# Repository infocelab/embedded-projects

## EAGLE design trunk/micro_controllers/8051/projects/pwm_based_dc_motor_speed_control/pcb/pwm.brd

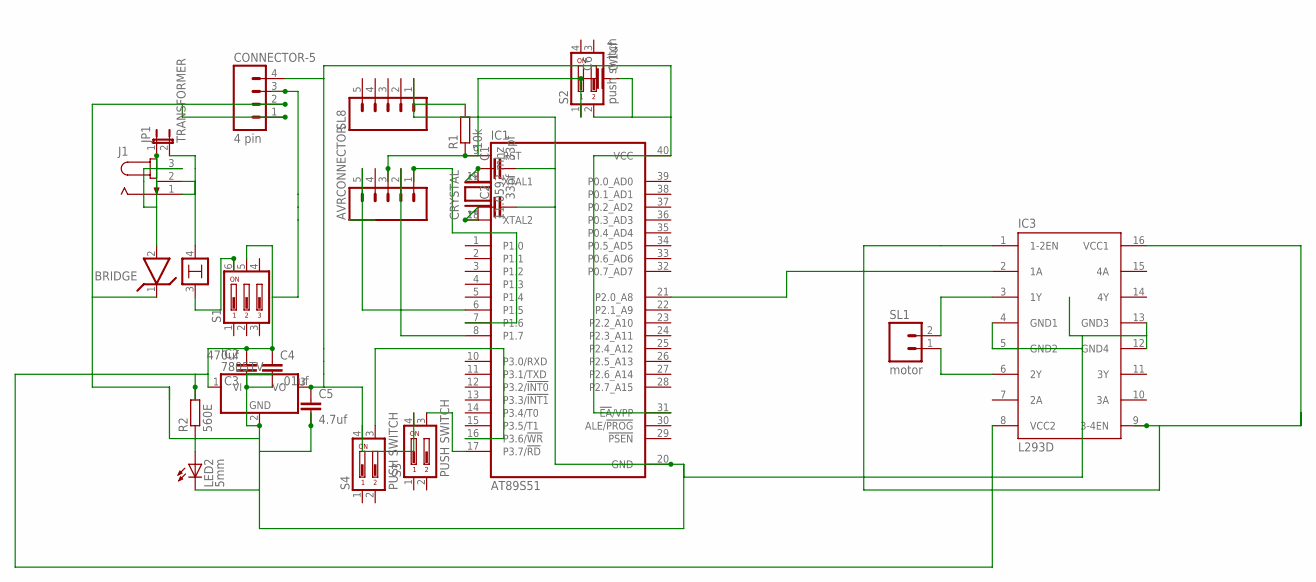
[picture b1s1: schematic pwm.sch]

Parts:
AVRCONNECTOR: M05; 05P
BRIDGE: LM399H; TO39/4
C1, C2: 33pf; C025-024X044
C3: 470uf; C5B7.2
C4: .01uf; C2.5-3
C5: 4.7uf; C2.5-3
C6: 0.1uf; C2.5-3
CONNECTOR-5: 4 pin; 04P
CRYSTAL: 11.0592 mhz; QS
IC1: AT89S51; DIL40
IC2: 7805TV; TO220V
IC3: L293D; DIL16
J1: JACK-PLUG0; SPC4077
JP1: TRANSFORMER; JP1
LED2: 5mm; LED5MM
R1: 10k; 0204/7
R2: 560E; 0204/7
S1: DA03; DA-03
S2: push switch; DP-02
S3, S4: PUSH SWITCH; DS-02
SL1: motor; 02P
SL8: M05; 05P

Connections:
unnamed: C2.1, CRYSTAL.1, IC1.18 (XTAL2)
unnamed: C1.1, CRYSTAL.2, IC1.19 (XTAL1)
unnamed: IC1.17 (P3.7/!RD), S3.3
unnamed: C3.2, C4.1, CONNECTOR-5.3, IC2.1 (VI), IC3.8 (VCC2), R2.2, S1.5
unnamed: BRIDGE.2, J1.3, JP1.1
unnamed: IC3.6 (2Y), SL1.1
unnamed: IC3.3 (1Y), SL1.2
unnamed: BRIDGE.1, CONNECTOR-5.1, CONNECTOR-5.2
unnamed: IC1.16 (P3.6/!WR), S4.3
unnamed: AVRCONNECTOR.3, C6.1, IC1.9 (RST), R1.1, S2.1
unnamed: AVRCONNECTOR.1, IC1.7 (P1.6)
unnamed: BRIDGE.4, J1.1, J1.2, JP1.2
unnamed: C1.2, C2.2, C3.1, C4.2, C5.2, IC1.20 (GND), IC2.2 (GND), IC3.4 (GND1), IC3.5 (GND2), IC3.12 (GND4), IC3.13 (GND3), LED2.K (C), R1.2, SL8.1
unnamed: IC3.1 (1-2EN), IC3.9 (3-4EN), IC3.16 (VCC1)
unnamed: IC1.21 (P2.0_A8), IC3.2 (1A)
unnamed: C5.1, C6.2, CONNECTOR-5.4, IC1.31 (!EA!/VPP), IC1.40 (VCC), IC2.3 (VO), S2.2, S3.4, S4.4
unnamed: AVRCONNECTOR.5, IC1.6 (P1.5)
unnamed: LED2.A, R2.1
unnamed: AVRCONNECTOR.2, IC1.8 (P1.7)
unnamed: BRIDGE.3, S1.6

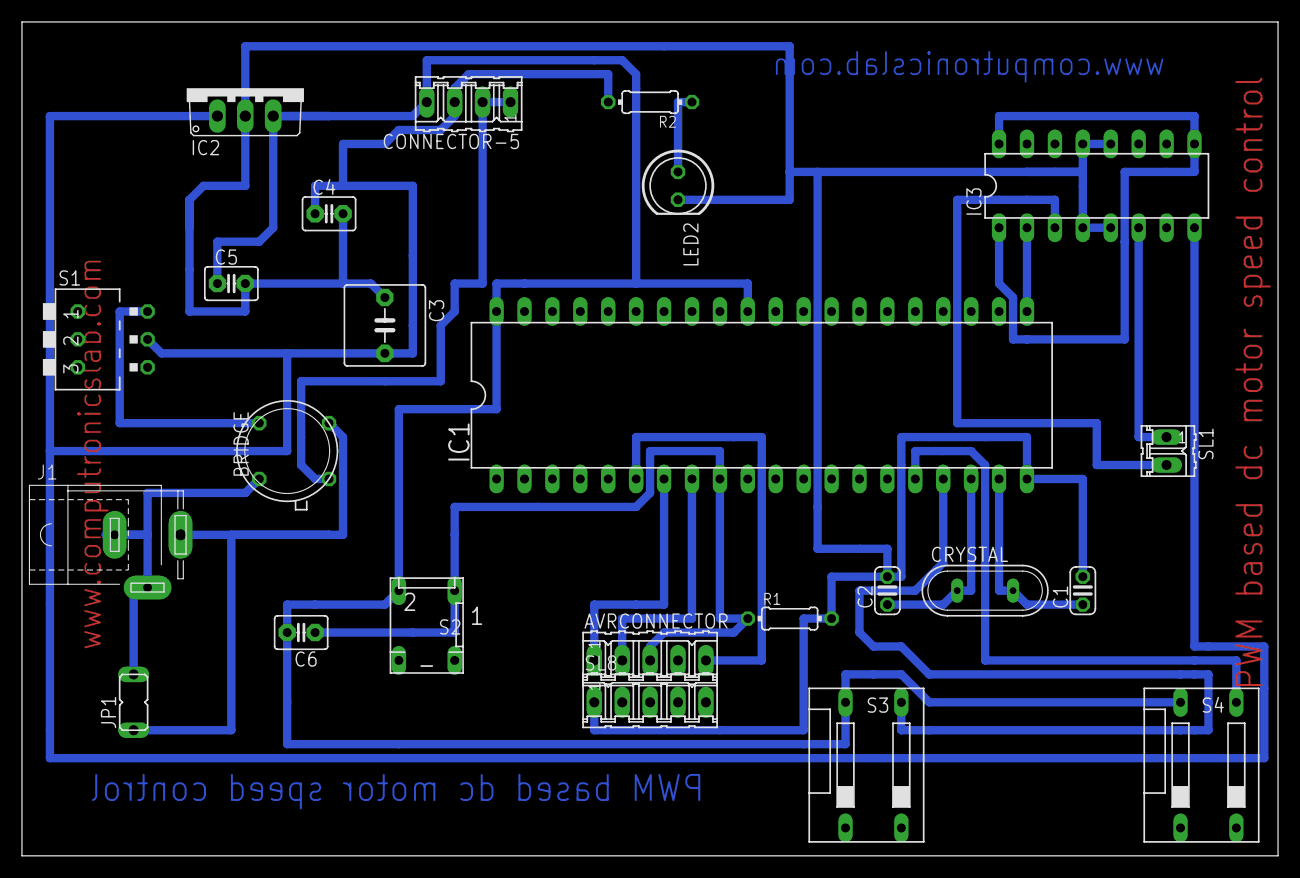
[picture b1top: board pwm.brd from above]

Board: 2 copper layers, 114.3 x 75.9 mm, 24 parts (0 on the bottom side), 20 nets.

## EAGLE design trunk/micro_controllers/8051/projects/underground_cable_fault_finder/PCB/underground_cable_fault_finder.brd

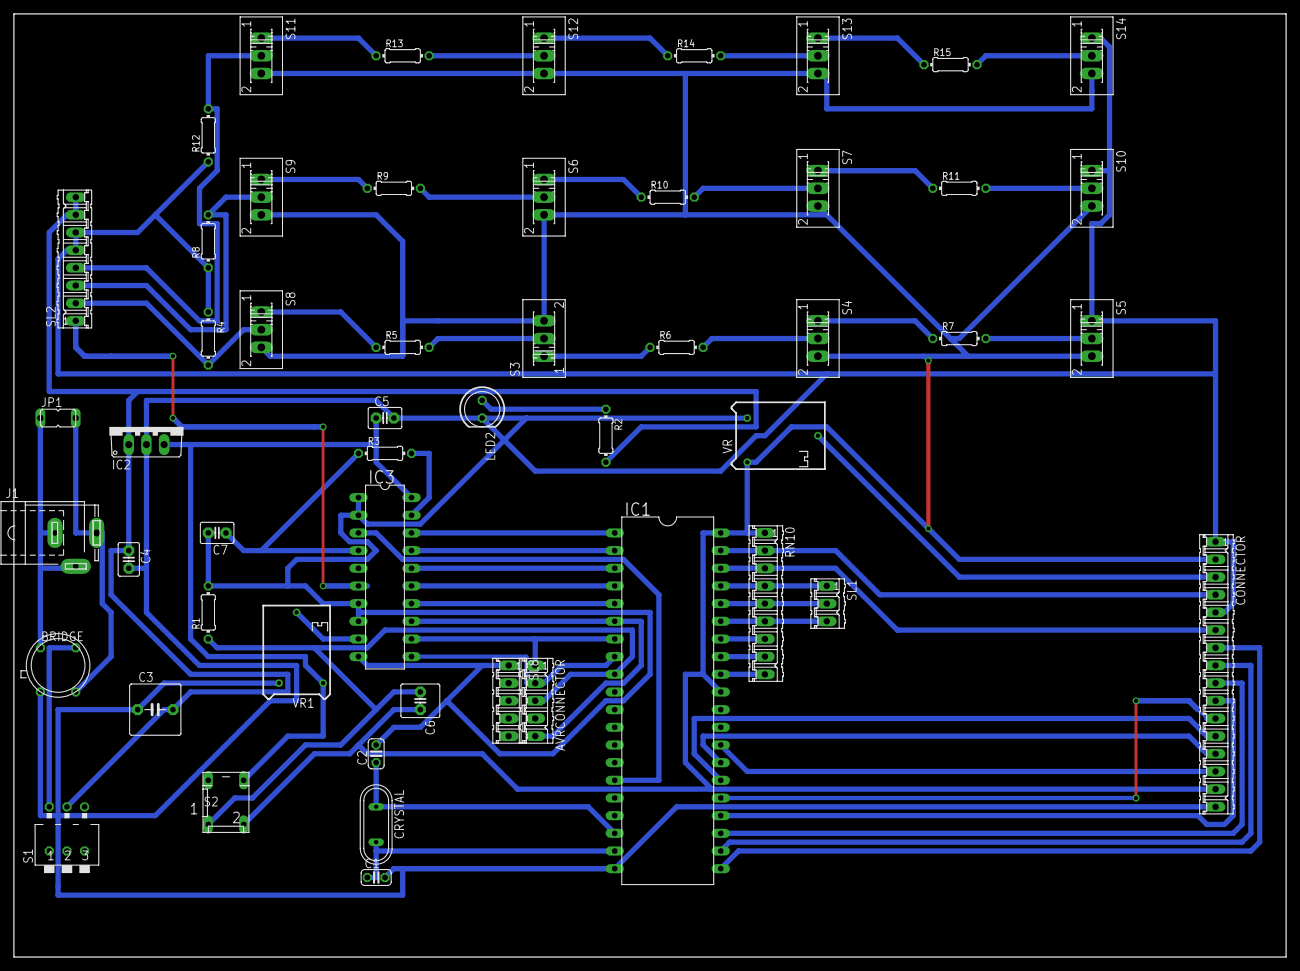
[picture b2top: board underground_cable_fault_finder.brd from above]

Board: 2 copper layers, 182.9 x 135.6 mm, 52 parts (0 on the bottom side), 62 nets.

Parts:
AVRCONNECTOR: 05P
BRIDGE: TO39/4
C1, C2: 33pf; C025-024X044
C3: 470uf; C5B7.2
C4: .01uf; C2.5-3
C5: 4.7uf; C2.5-3
C6: 0.1uf; C2.5-6
C7: 150pf; C2.5-3
CONNECTOR: LCD; 16P
CRYSTAL: 11.0592 mhz; QS
IC1: AT89S51; DIL40
IC2: 7805TV; TO220V
IC3: adc804; DIL20
J1: SPC4077
JP1: TRANSFORMER; JP1
LED2: 5mm; LED5MM
R1, R3, R4, R5, R6, R7, R8, R9, R10, R11, R12, R13, R14, R15: 10k; 0204/7
R2: 560E; 0204/7
RN10: 10 k; 09P
S1: ON/ OFF SWITCH; DA-03
S2: push switch; DP-02
S3, S4, S5, S6, S7, S8, S9, S10, S11, S12, S13, S14: 255SB
SL1: 03P
SL2: 08P
SL8: 05P
VR, VR1: 10k; RTRIM64P

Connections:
unnamed: C2.1, CRYSTAL.1, IC1.18
unnamed: C1.1, CRYSTAL.2, IC1.19
unnamed: BRIDGE.1, C1.2, C2.2, C3.1, C4.2, C5.2, C7.2, CONNECTOR.1, CONNECTOR.5, CONNECTOR.16, IC1.20, IC2.2, IC3.1, IC3.2, IC3.7, IC3.8, IC3.10, LED2.K, R1.2, R4.1, R8.1, R12.1, S5.1, S10.1, S14.1, SL2.5, SL2.6, SL8.1, VR.3, VR1.3
unnamed: BRIDGE.2, J1.3, JP1.2
unnamed: IC1.1, IC3.18
unnamed: IC1.2, IC3.17
unnamed: IC1.3, IC3.16
unnamed: IC1.4, IC3.15
unnamed: IC1.5, IC3.14
unnamed: AVRCONNECTOR.5, IC1.6, IC3.13
unnamed: AVRCONNECTOR.1, IC1.7, IC3.12
unnamed: AVRCONNECTOR.3, C6.1, IC1.9, R1.1, S2.1
unnamed: BRIDGE.4, J1.1, J1.2, JP1.1
unnamed: IC3.19, R3.2
unnamed: C7.1, IC3.4, R3.1
unnamed: R4.2, S8.2, SL2.2
unnamed: C6.2, CONNECTOR.2, CONNECTOR.15, IC1.31, IC1.40, RN10.1, S2.2, S3.3, S4.3, S5.3, S6.3, S7.3, S8.3, S9.3, S10.3, S11.3, S12.3, S13.3, S14.3, VR.1
unnamed: R8.2, S9.2, SL2.3
unnamed: R5.2, S3.2
unnamed: IC3.9, VR1.2
unnamed: IC1.36, RN10.5, SL1.2
unnamed: IC1.15, IC3.3
unnamed: IC1.34, RN10.7
unnamed: IC1.33, RN10.8
unnamed: IC1.32, RN10.9
unnamed: CONNECTOR.7, IC1.21
unnamed: CONNECTOR.8, IC1.22
unnamed: CONNECTOR.9, IC1.23
unnamed: R5.1, S8.1
unnamed: R6.2, S4.2
unnamed: CONNECTOR.12, IC1.26
unnamed: R6.1, S3.1
unnamed: R7.2, S5.2
unnamed: CONNECTOR.3, VR.2
unnamed: IC3.6, SL2.1
unnamed: R9.1, S9.1
unnamed: R9.2, S6.2
unnamed: LED2.A, R2.1
unnamed: R10.1, S6.1
unnamed: AVRCONNECTOR.2, IC1.8, IC3.11
unnamed: BRIDGE.3, S1.6
unnamed: CONNECTOR.6, IC1.38, RN10.3
unnamed: R10.2, S7.2
unnamed: R11.1, S7.1
unnamed: CONNECTOR.10, IC1.24
unnamed: CONNECTOR.11, IC1.25
unnamed: R11.2, S10.2
unnamed: CONNECTOR.13, IC1.27
unnamed: CONNECTOR.14, IC1.28
unnamed: C5.1, IC2.3, IC3.20, S2.3, VR1.1
unnamed: CONNECTOR.4, IC1.39, RN10.2
unnamed: R13.2, S12.2
unnamed: R14.2, S13.2
unnamed: R15.2, S14.2
unnamed: R13.1, S11.1
unnamed: R14.1, S12.1
unnamed: R15.1, S13.1
unnamed: C3.2, C4.1, IC2.1, R2.2, S1.5, SL2.7, SL2.8
unnamed: IC1.37, RN10.4, SL1.1
unnamed: R12.2, S11.2, SL2.4
unnamed: IC1.35, RN10.6, SL1.3
unnamed: R7.1, S4.1

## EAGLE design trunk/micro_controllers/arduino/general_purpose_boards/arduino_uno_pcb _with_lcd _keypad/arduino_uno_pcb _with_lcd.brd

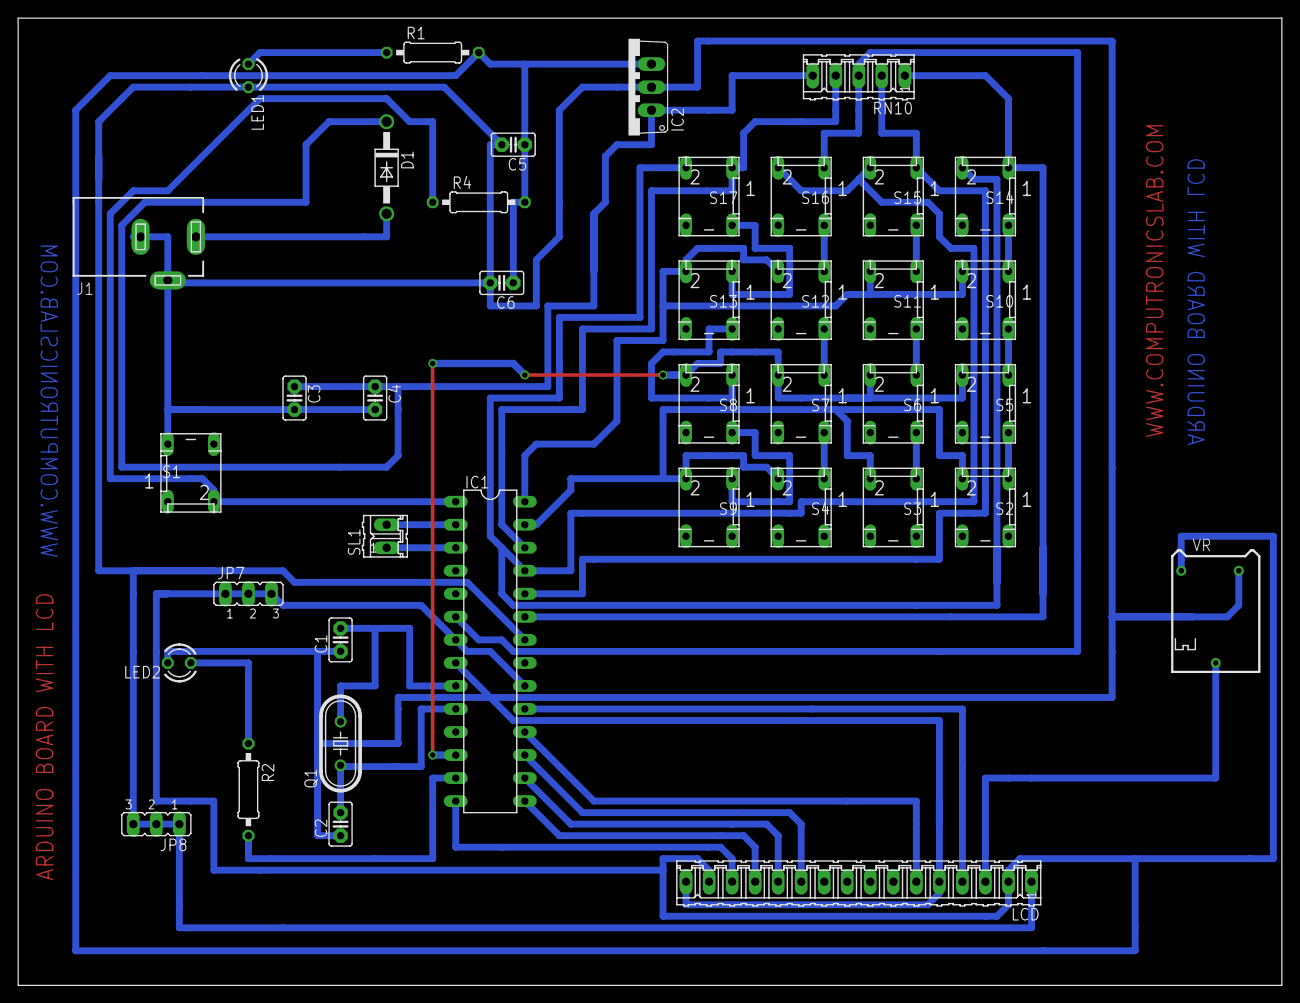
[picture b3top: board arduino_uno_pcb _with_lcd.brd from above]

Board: 2 copper layers, 139.4 x 106.7 mm, 39 parts (0 on the bottom side), 39 nets.

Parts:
C1, C2: 22pf; C2.5-2
C3: 100UF; C2.5-2
C4, C5: 0.1uf; C2.5-2
C6: 4.7uf; C2.5-2
D1: 1N4007; DO41-10
IC1: ATMEGA328; DIL28-3
IC2: 7805; TO220V
J1: DCJ0303
JP7, JP8: JP2
LCD: 16P
LED1, LED2: LED3MM
Q1: 16MHZ; HC49/S
R1: 220R; 0207/10
R2: 330R; 0207/10
R4: 10K; 0207/10
RN10: 5pin; 05P
S1, S4, S5, S6, S7, S8, S9, S10, S11, S12, S13, S14, S15, S16, S17: DP-02
S2, S3: push switch; DP-02
SL1: 02P
VR: 100k; RTRIM64P

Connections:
unnamed: C1.2, IC1.9, Q1.2
unnamed: C2.2, IC1.10, Q1.1
unnamed: D1.A, J1.1
unnamed: C5.1, C6.1, IC1.7, IC1.20, IC2.3, JP7.1, JP7.2, JP7.3, LCD.2, LCD.15, R1.2, R4.2, VR.1
unnamed: C1.1, C2.1, C3.2, C4.2, C5.2, C6.2, IC1.8, IC1.22, IC2.2, J1.2, J1.3, JP8.1, JP8.2, JP8.3, LCD.1, LCD.5, LCD.16, LED1.K, LED2.K, S1.4, VR.3
unnamed: LED1.A, R1.1
unnamed: C3.1, C4.1, D1.C, IC2.1, RN10.5
unnamed: IC1.26, RN10.4, S17.1
unnamed: IC1.25, S14.2, S15.2, S16.2, S17.2
unnamed: IC1.6, RN10.3, S16.1
unnamed: IC1.13, R2.2
unnamed: IC1.2, SL1.2
unnamed: IC1.3, SL1.1
unnamed: IC1.24, RN10.2, S15.1
unnamed: IC1.27, S2.2, S3.2, S4.2, S9.2
unnamed: LCD.3, VR.2
unnamed: IC1.19, LCD.4
unnamed: IC1.18, LCD.6
unnamed: IC1.17, LCD.11
unnamed: IC1.16, LCD.12
unnamed: IC1.15, LCD.13
unnamed: IC1.14, LCD.14
unnamed: IC1.1, R4.1, S1.2
unnamed: LED2.A, R2.1
unnamed: IC1.12, S5.2, S6.2, S7.2, S8.2
unnamed: IC1.28, S10.2, S11.2, S12.2, S13.2
unnamed: S2.1, S5.4
unnamed: S5.1, S10.4
unnamed: S10.1, S14.4
unnamed: S6.1, S11.4
unnamed: S11.1, S15.4
unnamed: S12.1, S16.4
unnamed: S13.1, S17.4
unnamed: S8.1, S13.4
unnamed: IC1.23, RN10.1, S14.1
unnamed: S3.1, S6.4
unnamed: S4.1, S7.4
unnamed: S8.4, S9.1
unnamed: S7.1, S12.4

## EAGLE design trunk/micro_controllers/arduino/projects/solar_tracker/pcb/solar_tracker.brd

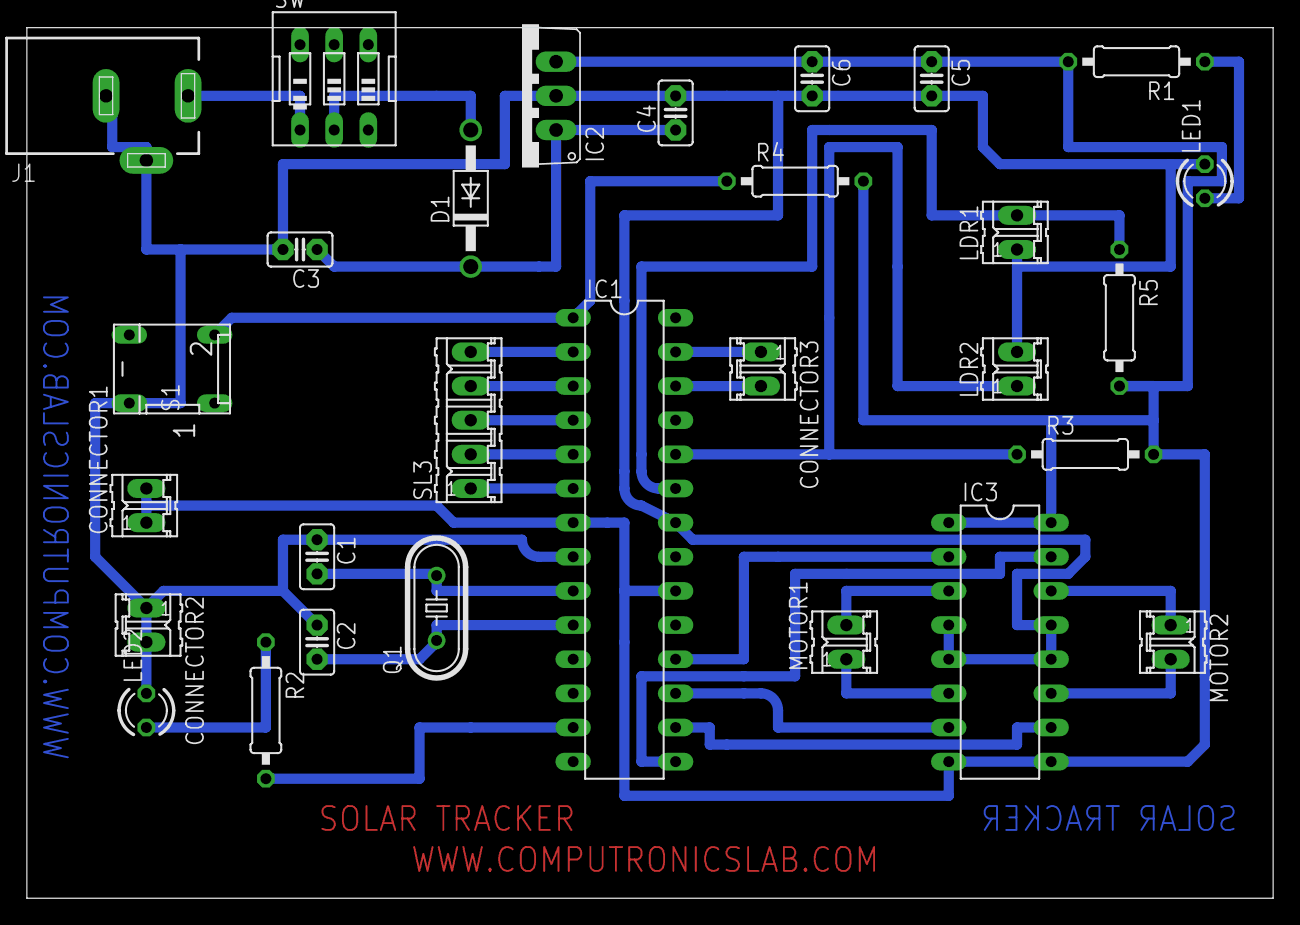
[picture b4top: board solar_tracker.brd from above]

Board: 2 copper layers, 92.7 x 64.8 mm, 29 parts (0 on the bottom side), 28 nets.

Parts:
C1, C2: 22pf; C2.5-2
C3: 100uF; C2.5-2
C4, C5: 0.1uf; C2.5-2
C6: 4.7uf; C2.5-2
CONNECTOR1: 2pin; 02P
CONNECTOR2: 2 pin; 02P
CONNECTOR3: 02P
D1: 1N4007; DO41-10
IC1: ATMEGA328; DIL28-3
IC2: 7805; TO220V
IC3: L293D; DIL16
J1: DCJ0303
LDR1, LDR2: 02P
LED1, LED2: 3mm; LED3MM
MOTOR1, MOTOR2: 02P
Q1: 16MHZ; HC49/S
R1: 220R; 0207/10
R2: 330R; 0207/10
R3, R4, R5: 10K; 0207/10
S1: push switch; DP-02
SL3: 5 pin; 05P
SW: on/of button; EDG-03

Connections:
unnamed: C1.2, IC1.9, Q1.2
unnamed: C2.2, IC1.10, Q1.1
unnamed: J1.1, SW.1
unnamed: C5.1, C6.1, CONNECTOR1.1, CONNECTOR1.2, IC1.7, IC1.20, IC2.3, IC3.1, IC3.8, IC3.9, IC3.16, R1.2, R3.2, R4.2, R5.2
unnamed: C1.1, C2.1, C3.2, C4.2, C5.2, C6.2, CONNECTOR2.1, CONNECTOR2.2, IC1.8, IC1.22, IC2.2, IC3.4, IC3.5, IC3.12, IC3.13, J1.2, J1.3, LDR1.1, LDR2.2, LED1.K, LED2.K, S1.4
unnamed: LED1.A, R1.1
unnamed: IC1.17, IC3.7
unnamed: IC1.6, SL3.1
unnamed: IC1.5, SL3.2
unnamed: IC1.4, SL3.3
unnamed: IC1.3, SL3.4
unnamed: CONNECTOR3.1, IC1.27
unnamed: CONNECTOR3.2, IC1.26
unnamed: IC1.2, SL3.5
unnamed: IC1.18, IC3.2
unnamed: IC1.15, IC3.15
unnamed: IC1.13, R2.2
unnamed: D1.A, SW.2
unnamed: IC1.23, LDR1.2, R5.1
unnamed: IC1.24, LDR2.1, R3.1
unnamed: IC1.16, IC3.10
unnamed: C3.1, C4.1, D1.C, IC2.1
unnamed: IC3.14, MOTOR2.1
unnamed: IC3.11, MOTOR2.2
unnamed: IC1.1, R4.1, S1.2
unnamed: LED2.A, R2.1
unnamed: IC3.6, MOTOR1.1
unnamed: IC3.3, MOTOR1.2
